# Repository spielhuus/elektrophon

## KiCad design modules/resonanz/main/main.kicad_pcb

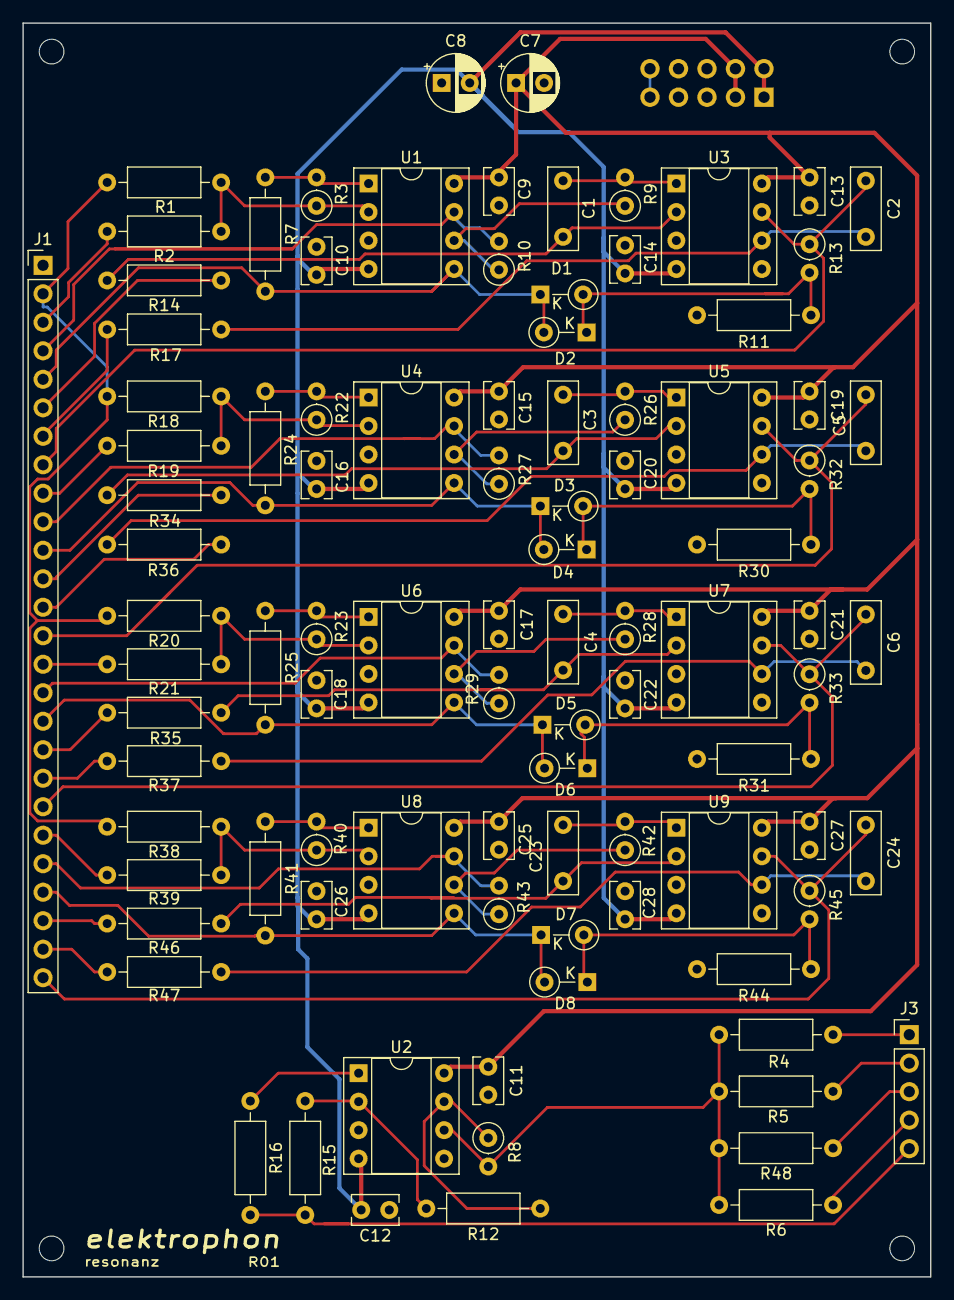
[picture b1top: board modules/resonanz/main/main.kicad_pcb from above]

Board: 2 copper layers, 80.9 x 111.8 mm, 101 parts (1 on the bottom side), 66 nets.

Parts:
C1, C2, C3, C4, C5, C6, C23, C24: 22n polyester; C_Rect_L7.2mm_W2.5mm_P5.00mm_FKS2_FKP2_MKS2_MKP2
C7, C8: 10u; CP_Radial_D5.0mm_P2.50mm
C9, C10, C11, C12, C13, C14, C15, C16, C17, C18, C19, C20, C21, C22, C25, C26, C27, C28: 0.1u; C_Rect_L4.0mm_W2.5mm_P2.50mm
D1, D2, D3, D4, D5, D6, D7, D8: 1N4148; D_DO-35_SOD27_P3.81mm_Vertical_KathodeUp
H1, H2, H3, H4: MountingHole; MountingHole_2.2mm_M2
J1: Conn_01x26_Female; PinHeader_1x26_P2.54mm_Vertical
J2: IDC Header; IDC-Header_2x05_P2.54mm_Vertical
J3: Conn_01x05_Female; PinHeader_1x05_P2.54mm_Vertical
R1, R2, R18, R19, R20, R21, R38, R39: 47k; R_Axial_DIN0207_L6.3mm_D2.5mm_P10.16mm_Horizontal
R3, R22, R23, R40: 47k; R_Axial_DIN0207_L6.3mm_D2.5mm_P2.54mm_Vertical
R4, R5, R6, R12, R15, R48: 100k; R_Axial_DIN0207_L6.3mm_D2.5mm_P10.16mm_Horizontal
R7, R24, R25, R41: 10k; R_Axial_DIN0207_L6.3mm_D2.5mm_P10.16mm_Horizontal
R8: 100k; R_Axial_DIN0207_L6.3mm_D2.5mm_P2.54mm_Vertical
R9, R10, R26, R27, R28, R29, R42, R43: 10k; R_Axial_DIN0207_L6.3mm_D2.5mm_P2.54mm_Vertical
R11, R30, R31, R44: 15k; R_Axial_DIN0207_L6.3mm_D2.5mm_P10.16mm_Horizontal
R13, R32, R33, R45: 6k8; R_Axial_DIN0207_L6.3mm_D2.5mm_P2.54mm_Vertical
R14, R17, R34, R35, R36, R37, R46, R47: 680; R_Axial_DIN0207_L6.3mm_D2.5mm_P10.16mm_Horizontal
R16: 1k; R_Axial_DIN0207_L6.3mm_D2.5mm_P10.16mm_Horizontal
REF1: elektrophon logo
U1, U3, U4, U5, U6, U7, U8, U9: LM1458; DIP-8_W7.62mm_Socket
U2: TL072; DIP-8_W7.62mm_Socket

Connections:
+5V: J2.9, J2.10
+15V: C7.1, C9.1, C11.1, C13.1, C15.1, C17.1, C19.1, C21.1, C25.1, C27.1, J2.3, J2.4, U1.8, U2.8, U3.8, U4.8, U5.8, U6.8, U7.8, U8.8, U9.8
-15V: C8.2, C10.2, C12.2, C14.2, C16.2, C18.2, C20.2, C22.2, C26.2, C28.2, J2.1, J2.2, U1.4, U2.4, U3.4, U4.4, U5.4, U6.4, U7.4, U8.4, U9.4
FREQ_1_a: J1.4, R10.2, U1.7
FREQ_1_b: J1.7, R17.2
FREQ_1_c: J1.6, R14.2
FREQ_2_a: J1.10, R27.2, U4.7
FREQ_2_b: J1.13, R36.2
FREQ_2_c: J1.12, R34.2
FREQ_3_a: J1.16, R29.2, U6.7
FREQ_3_b: J1.19, R37.2
FREQ_3_c: J1.18, R35.2
FREQ_4_a: J1.22, R43.2, U8.7
FREQ_4_b: J1.25, R47.2
FREQ_4_c: J1.24, R46.2
GND: C7.2, C8.1, C9.2, C10.1, C11.2, C12.1, C13.2, C14.1, C15.2, C16.1, C17.2, C18.1, C19.2, C20.1, C21.2, C22.1, C25.2, C26.1, C27.2, C28.1, J1.1, J2.5, J2.6, J2.7, J2.8, R11.2, R30.2, R31.2, R44.2, U1.3, U2.3, U2.5, U3.3, U3.5, U4.3, U5.3, U5.5, U6.3, U7.3, U7.5, U8.3, U9.3, U9.5
IN: J1.2, R1.1, R18.1, R20.1, R38.1
IN_1: J1.3, R2.1
IN_2: J1.9, R19.1
IN_3: J1.15, R21.1
IN_4: J1.21, R39.1
MIX_1: J3.1, R4.2
MIX_2: J3.2, R5.2
MIX_3: J3.3, R48.2
MIX_4: J3.4, R6.2
unnamed: C1.1, R9.2, U3.1
unnamed: C1.2, R14.1, U3.2
unnamed: C2.2, R17.1, U3.6
unnamed: C3.1, R26.2, U5.1
unnamed: C3.2, R34.1, U5.2
unnamed: C4.1, R28.2, U7.1
unnamed: C4.2, R35.1, U7.2
unnamed: C5.2, R36.1, U5.6
unnamed: C6.2, R37.1, U7.6
unnamed: C23.1, R42.2, U9.1
unnamed: C23.2, R46.1, U9.2
unnamed: C24.2, R47.1, U9.6
unnamed: D1.2, D2.1, R11.1, R13.2
unnamed: D3.2, D4.1, R30.1, R32.2
unnamed: D5.2, D6.1, R31.1, R33.2
unnamed: D7.2, D8.1, R44.1, R45.2
unnamed: R1.2, R2.2, R3.1, U1.2
unnamed: R3.2, R7.1, U1.1
unnamed: R4.1, R5.1, R6.1, R8.2, R48.1, U2.6
unnamed: R9.1, R10.1, U1.6
unnamed: R12.1, R15.2, U2.2
unnamed: R8.1, R12.2, U2.7
unnamed: R16.2, U2.1
unnamed: R18.2, R19.2, R22.1, U4.2
unnamed: R20.2, R21.2, R23.1, U6.2
unnamed: R22.2, R24.1, U4.1
unnamed: R23.2, R25.1, U6.1
unnamed: R26.1, R27.1, U4.6
unnamed: R28.1, R29.1, U6.6
unnamed: R38.2, R39.2, R40.1, U8.2
unnamed: R40.2, R41.1, U8.1
unnamed: R42.1, R43.1, U8.6
OUT: J3.5, R15.1, R16.1
OUT_1: C2.1, J1.8, R13.1, U3.7
OUT_2: C5.1, J1.14, R32.1, U5.7
OUT_3: C6.1, J1.20, R33.1, U7.7
OUT_4: C24.1, J1.26, R45.1, U9.7
RES_1: D1.1, D2.2, J1.5, R7.2, U1.5
RES_2: D3.1, D4.2, J1.11, R24.2, U4.5
RES_3: D5.1, D6.2, J1.17, R25.2, U6.5
RES_4: D7.1, D8.2, J1.23, R41.2, U8.5

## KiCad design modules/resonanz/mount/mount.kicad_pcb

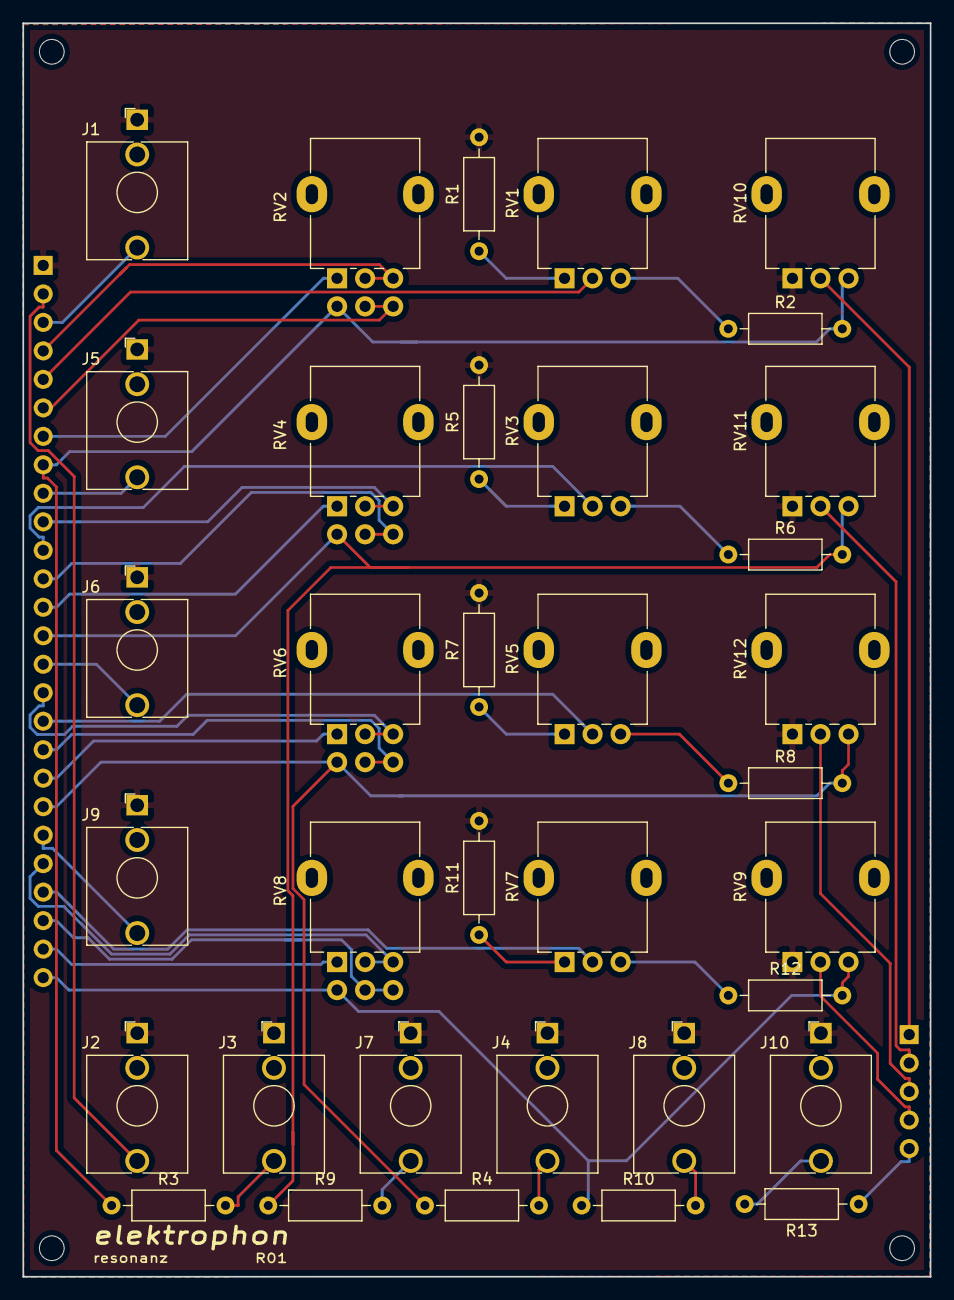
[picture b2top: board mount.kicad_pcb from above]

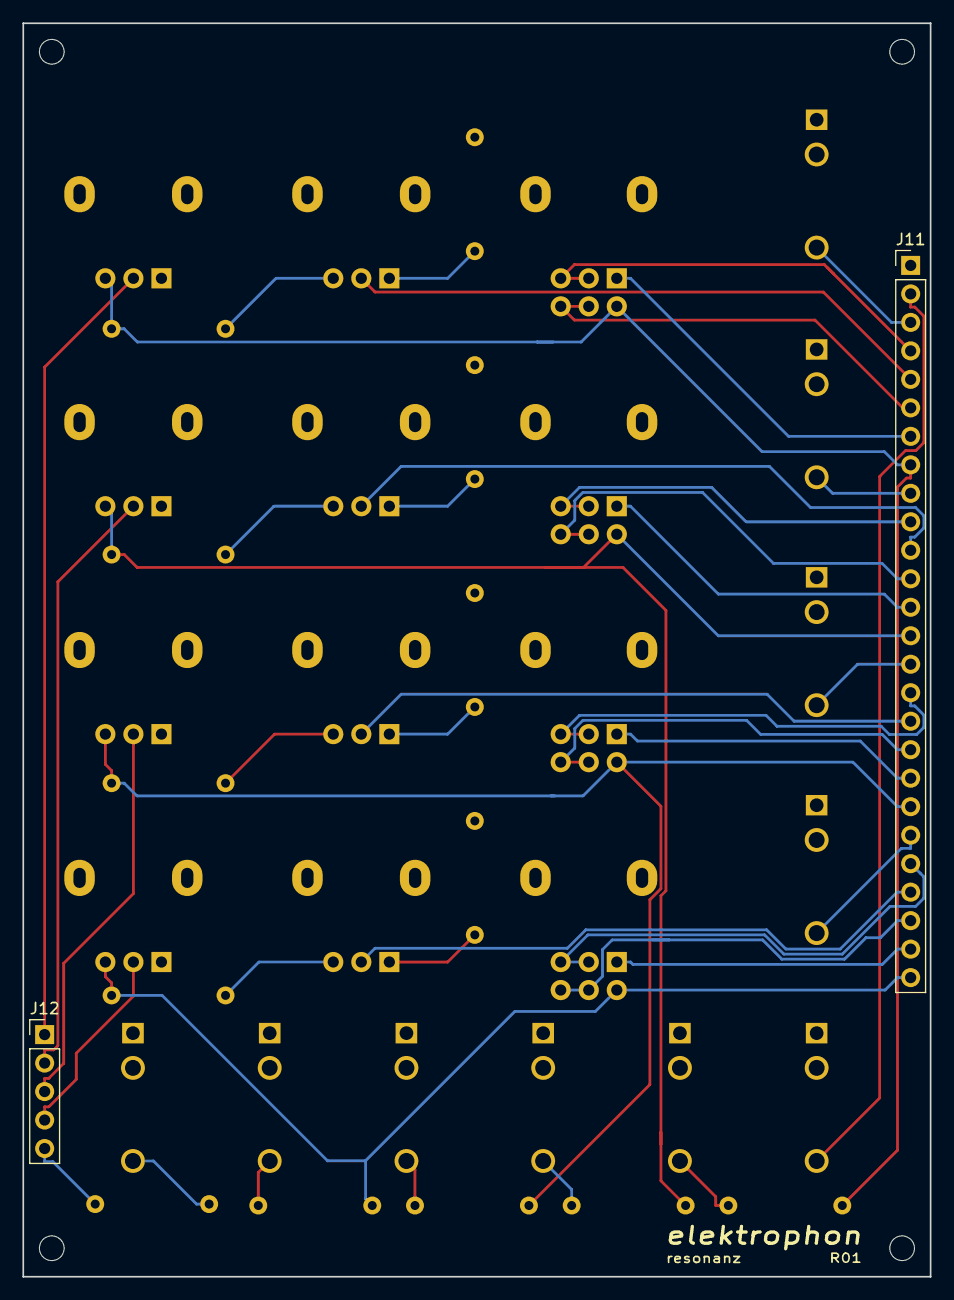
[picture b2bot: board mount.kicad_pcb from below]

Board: 2 copper layers, 80.9 x 111.8 mm, 41 parts (2 on the bottom side), 44 nets.

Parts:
H1, H2, H3, H4: MountingHole; MountingHole_2.2mm_M2
J1, J2, J3, J4, J5, J6, J7, J8, J9, J10: AudioJack2_SwitchT; Jack_3.5mm_WQP-PJ398SM_Vertical
J11: Conn_01x26_Male; PinHeader_1x26_P2.54mm_Vertical
J12: Conn_01x05_Male; PinHeader_1x05_P2.54mm_Vertical
R1, R5, R7, R11: 470; R_Axial_DIN0207_L6.3mm_D2.5mm_P10.16mm_Horizontal
R2, R6, R8, R12: 22k; R_Axial_DIN0207_L6.3mm_D2.5mm_P10.16mm_Horizontal
R3, R4, R9, R10, R13: 1k; R_Axial_DIN0207_L6.3mm_D2.5mm_P10.16mm_Horizontal
RV1, RV3, RV5, RV7: 50k; Potentiometer_Alpha_RD901F-40-00D_Single_Vertical
RV2, RV4, RV6, RV8: 100k; Potentiometer_Alpha_RD902F-40-00D_Dual_Vertical
RV9, RV10, RV11, RV12: 100k; Potentiometer_Alpha_RD901F-40-00D_Single_Vertical

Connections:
FREQ_1_a: J11.4, RV2.2, RV2.3
FREQ_1_b: J11.7, RV2.1
FREQ_1_c: J11.6, RV2.5, RV2.6
FREQ_2_a: J11.10, RV4.2, RV4.3
FREQ_2_b: J11.13, RV4.1
FREQ_2_c: J11.12, RV4.5, RV4.6
FREQ_3_a: J11.16, RV6.2, RV6.3
FREQ_3_b: J11.19, RV6.1
FREQ_3_c: J11.18, RV6.5, RV6.6
FREQ_4_a: J11.22, RV8.2, RV8.3
FREQ_4_b: J11.25, RV8.1
FREQ_4_c: J11.24, RV8.5, RV8.6
GND: J1.S, J2.S, J3.S, J4.S, J5.S, J6.S, J7.S, J8.S, J9.S, J10.S, J11.1, R1.2, R5.2, R7.2, R11.2, RV9.1, RV10.1, RV11.1, RV12.1
IN: J2.T, J11.2
IN_1: J1.T, J11.3
IN_2: J5.T, J11.9
IN_3: J6.T, J11.15
IN_4: J9.T, J11.21
MIX_1: J12.1, RV10.2
MIX_2: J12.2, RV11.2
MIX_3: J12.3, RV12.2
MIX_4: J12.4, RV9.2
unnamed: J3.T, R3.2
unnamed: J4.T, R4.2
unnamed: J7.T, R9.2
unnamed: J8.T, R10.2
unnamed: J10.T, R13.2
unnamed: R1.1, RV1.1
unnamed: R2.1, RV1.3
unnamed: R5.1, RV3.1
unnamed: R6.1, RV3.3
unnamed: R7.1, RV5.1
unnamed: R8.1, RV5.3
unnamed: R11.1, RV7.1
unnamed: R12.1, RV7.3
OUT: J12.5, R13.1
OUT_1: J11.8, R2.2, R3.1, RV2.4, RV10.3
OUT_2: J11.14, R6.2, R9.1, RV4.4, RV11.3
OUT_3: J11.20, R4.1, R8.2, RV6.4, RV12.3
OUT_4: J11.26, R10.1, R12.2, RV8.4, RV9.3
RES_1: J11.5, RV1.2
RES_2: J11.11, RV3.2
RES_3: J11.17, RV5.2
RES_4: J11.23, RV7.2

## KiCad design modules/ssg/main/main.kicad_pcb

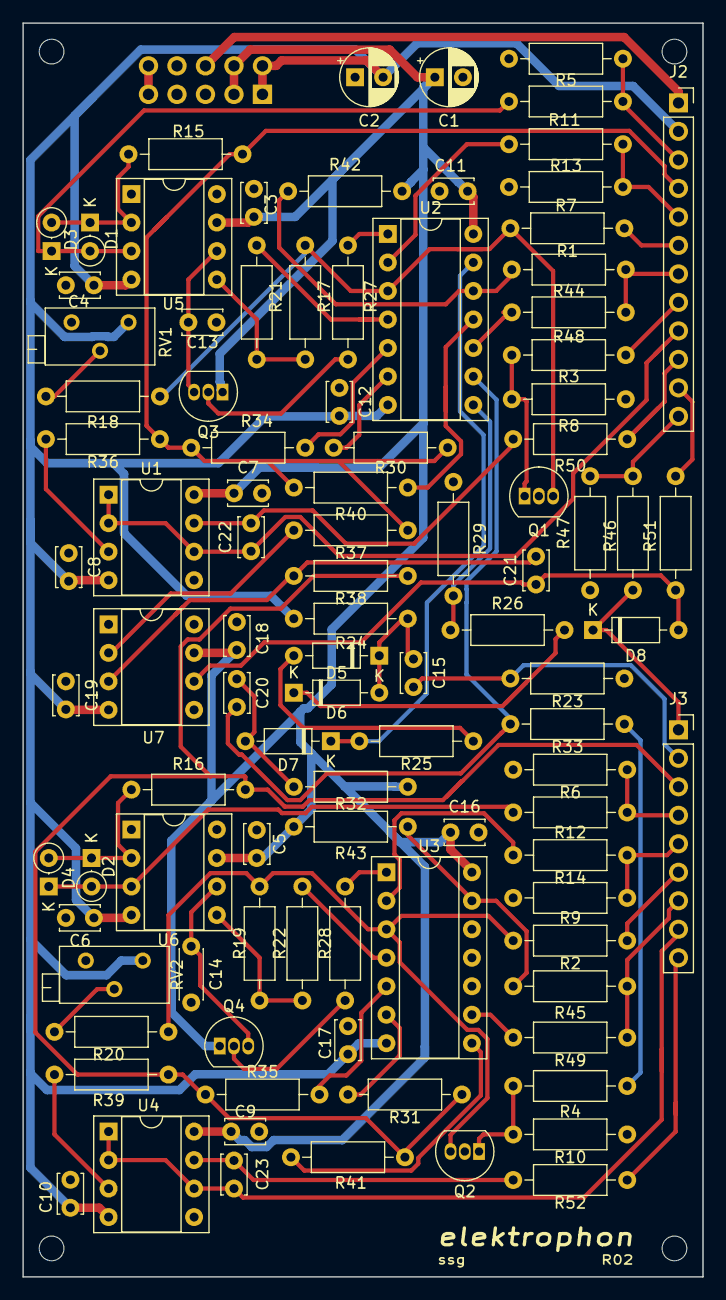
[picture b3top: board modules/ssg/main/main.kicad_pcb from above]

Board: 2 copper layers, 60.6 x 111.8 mm, 99 parts (1 on the bottom side), 70 nets.

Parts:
C1, C2: 10u; CP_Radial_D5.0mm_P2.50mm
C3, C4, C5, C6, C7, C8, C9, C10, C11, C12, C16, C17, C18, C19: 0.1u; C_Disc_D3.4mm_W2.1mm_P2.50mm
C13: 100n; C_Disc_D3.4mm_W2.1mm_P2.50mm
C14: 220n; C_Disc_D4.3mm_W1.9mm_P5.00mm
C15, C20: 1n; C_Disc_D3.4mm_W2.1mm_P2.50mm
C21: 100p; C_Disc_D3.4mm_W2.1mm_P2.50mm
C22, C23: 47p; C_Disc_D3.4mm_W2.1mm_P2.50mm
D1, D2, D3, D4: 1N4148; D_DO-35_SOD27_P2.54mm_Vertical_KathodeUp
D5, D6, D7, D8: 1N4148; D_DO-35_SOD27_P7.62mm_Horizontal
J1: IDC Header; IDC-Header_2x05_P2.54mm_Vertical
J2: Conn_01x12_Female; PinSocket_1x12_P2.54mm_Vertical
J3: Conn_01x09_Female; PinSocket_1x09_P2.54mm_Vertical
Q1, Q2: PN4250; TO-92_Inline
Q3, Q4: J201; TO-92_Inline
R1, R2, R13, R14: 2M7; R_Axial_DIN0207_L6.3mm_D2.5mm_P10.16mm_Horizontal
R3, R4, R5, R6, R11, R12, R15, R16, R24: 33k; R_Axial_DIN0207_L6.3mm_D2.5mm_P10.16mm_Horizontal
R7, R9, R23, R26: 100k; R_Axial_DIN0207_L6.3mm_D2.5mm_P10.16mm_Horizontal
R8, R10, R21, R22: 15k; R_Axial_DIN0207_L6.3mm_D2.5mm_P10.16mm_Horizontal
R17, R19: 82k; R_Axial_DIN0207_L6.3mm_D2.5mm_P10.16mm_Horizontal
R18, R20, R32: 1M5; R_Axial_DIN0207_L6.3mm_D2.5mm_P10.16mm_Horizontal
R25: 680k; R_Axial_DIN0207_L6.3mm_D2.5mm_P10.16mm_Horizontal
R27, R31: 820k; R_Axial_DIN0207_L6.3mm_D2.5mm_P10.16mm_Horizontal
R28, R30, R42, R43: 1M; R_Axial_DIN0207_L6.3mm_D2.5mm_P10.16mm_Horizontal
R29: 4M7; R_Axial_DIN0207_L6.3mm_D2.5mm_P10.16mm_Horizontal
R33, R34, R35: 330; R_Axial_DIN0207_L6.3mm_D2.5mm_P10.16mm_Horizontal
R36, R37, R38, R39: 10k; R_Axial_DIN0207_L6.3mm_D2.5mm_P10.16mm_Horizontal
R40, R41: 470k; R_Axial_DIN0207_L6.3mm_D2.5mm_P10.16mm_Horizontal
R44, R45: 2M2; R_Axial_DIN0207_L6.3mm_D2.5mm_P10.16mm_Horizontal
R46, R47, R48, R49, R51: 3k3; R_Axial_DIN0207_L6.3mm_D2.5mm_P10.16mm_Horizontal
R50, R52: 100; R_Axial_DIN0207_L6.3mm_D2.5mm_P10.16mm_Horizontal
RV1, RV2: 25k; Potentiometer_Bourns_3296Z_Horizontal
U1, U4: TL072; DIP-8_W7.62mm_Socket
U2, U3: LM3900; DIP-14_W7.62mm_Socket
U5, U6: CA3080; DIP-8_W7.62mm_Socket
U7: LM741; DIP-8_W7.62mm_Socket

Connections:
+5V: J1.9, J1.10
+15V: C1.1, C3.1, C5.1, C7.1, C9.1, C11.1, C16.1, C18.1, J1.3, J1.4, Q3.1, Q4.1, R32.2, R42.2, R43.2, U1.8, U2.14, U3.14, U4.8, U5.7, U6.7, U7.7
-15V: C2.2, C4.2, C6.2, C8.2, C10.2, C12.2, C17.2, C19.2, J1.1, J1.2, J2.2, R24.1, RV1.1, RV2.1, U1.4, U2.7, U3.7, U4.4, U5.4, U6.4, U7.4
/HOLD: R4.2, R33.1
COUPLER_5V: J2.12, R46.1, R47.2
COUPLER_HOT: J2.11, R51.1
CYCLE_1: J2.7, R44.1, R48.1
CYCLE_2: J3.7, R45.1, R49.1
GND: C1.2, C2.1, C3.2, C4.1, C5.2, C6.1, C7.2, C8.1, C9.2, C10.1, C11.2, C12.1, C13.2, C14.2, C16.2, C17.1, C18.2, C19.1, J1.5, J1.6, J1.7, J1.8, J2.1, Q1.2, Q2.2, R5.1, R6.1, R7.1, R8.1, R9.1, R10.1, R23.1, R29.1, R47.1, RV1.3, RV2.3, U1.5, U4.5
HOLD_1: J2.8, R3.2
IN_1: J2.3, R5.2, R11.2
IN_2: J3.4, R6.2, R12.2
LED: D8.1, J3.1, R46.2
LED_1_a: C22.1, J2.9, U1.1, U1.2, U1.6
LED_1_b: J2.10, R50.1
LED_2_a: C23.1, J3.8, U4.1, U4.2, U4.6
LED_2_b: J3.9, R52.1
unnamed: C13.1, Q3.3, U5.6
unnamed: C14.1, Q4.3, U6.6
unnamed: C15.2, D5.1, D6.2, R24.2
unnamed: C20.1, R33.2, U2.9
unnamed: C20.2, D7.2, R32.1
unnamed: C21.1, D8.2, R51.2, U7.6
unnamed: C21.2, R38.1, U7.3
unnamed: C22.2, R50.2, U1.7
unnamed: C23.2, R52.2, U4.7
unnamed: D1.1, D3.2, R15.2, U5.2
unnamed: D1.2, D3.1, R11.1, U5.3
unnamed: D2.1, D4.2, R16.2, U6.2
unnamed: D2.2, D4.1, R12.1, U6.3
unnamed: D5.2, R25.2
unnamed: D6.1, R26.2
unnamed: D7.1, R25.1, U2.13
unnamed: Q1.1, R3.1, R8.2
unnamed: Q1.3, R1.1, R17.2, R18.2, U2.3
unnamed: Q2.1, R4.1, R10.2
unnamed: Q2.3, R2.1, R19.2, R20.2, U3.3
unnamed: Q3.2, R27.2
unnamed: Q4.2, R28.2
unnamed: R13.1, U2.2
unnamed: R14.1, U3.2
unnamed: R17.1, R21.1, U5.5
unnamed: R18.1, RV1.2
unnamed: R19.1, R22.1, U6.5
unnamed: R20.1, RV2.2
unnamed: R21.2, U2.4
unnamed: R22.2, U3.4
unnamed: R26.1, R29.2, U2.8
unnamed: R27.1, U2.1
unnamed: R28.1, U3.1
unnamed: R30.1, U2.6
unnamed: R31.1, U3.6
unnamed: R34.2, U2.5
unnamed: R35.2, U3.5
unnamed: R36.1, U1.3
unnamed: R37.1, U7.2
unnamed: R39.1, U4.3
unnamed: R40.1, U2.11
unnamed: R41.1, U3.8
unnamed: R42.1, R44.2, U2.12
unnamed: R43.1, R45.2, U3.13
unnamed: R48.2, U2.10
unnamed: R49.2, U3.9
OUT_1: J2.4, R15.1, R30.2, R34.1, R36.2, R37.2, R40.2
OUT_2: J3.3, R16.1, R31.2, R35.1, R38.2, R39.2, R41.2
RATE_1: J2.6, R1.2
RATE_2: J3.6, R2.2
SAMPLE_2: C15.1, J3.2, R23.2
VC_1: J2.5, R7.2, R13.2
VC_2: J3.5, R9.2, R14.2

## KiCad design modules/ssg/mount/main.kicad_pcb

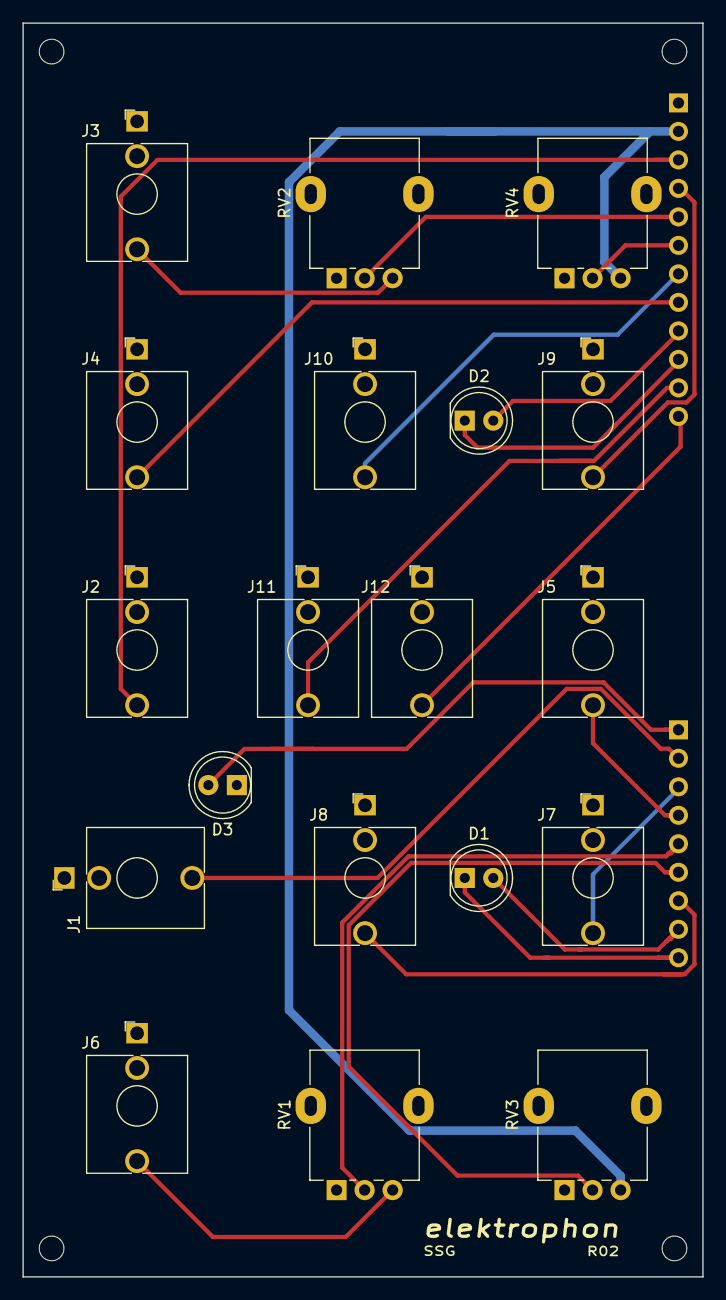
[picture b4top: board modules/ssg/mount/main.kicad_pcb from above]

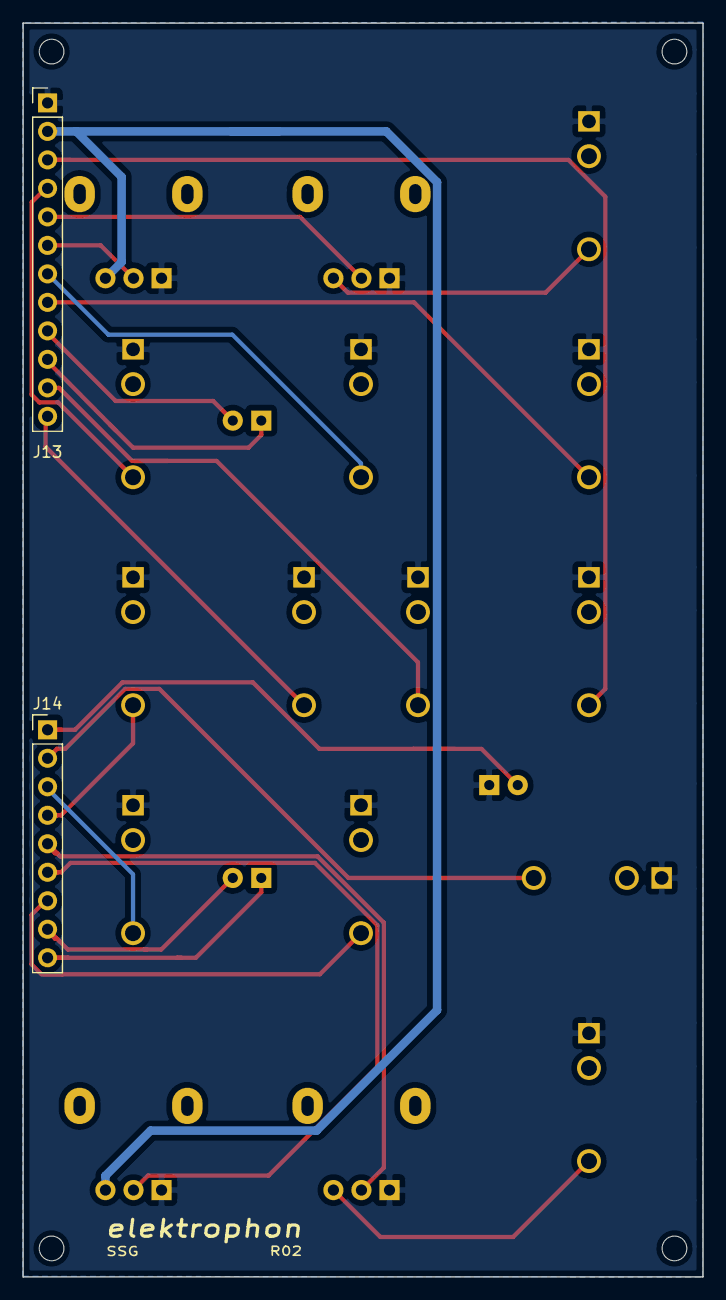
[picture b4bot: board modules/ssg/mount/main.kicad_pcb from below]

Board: 2 copper layers, 60.6 x 111.8 mm, 21 parts (2 on the bottom side), 23 nets.

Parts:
D1, D2: LED_Dual_2pin; LED_D5.0mm
D3: LED; LED_D5.0mm
J1: SAMPLE; Jack_3.5mm_WQP-PJ398SM_Vertical
J2, J5: IN; Jack_3.5mm_WQP-PJ398SM_Vertical
J3, J6: VC; Jack_3.5mm_WQP-PJ398SM_Vertical
J4: HOLD; Jack_3.5mm_WQP-PJ398SM_Vertical
J7, J9: OUT; Jack_3.5mm_WQP-PJ398SM_Vertical
J8, J10: CYCLE; Jack_3.5mm_WQP-PJ398SM_Vertical
J11: HOT; Jack_3.5mm_WQP-PJ398SM_Vertical
J12: 5V; Jack_3.5mm_WQP-PJ398SM_Vertical
J13: Conn_01x12_Male; PinHeader_1x12_P2.54mm_Vertical
J14: Conn_01x09_Male; PinHeader_1x09_P2.54mm_Vertical
RV1, RV2, RV3, RV4: 50k; Potentiometer_Alpha_RD901F-40-00D_Single_Vertical

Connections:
-15V: J13.2, RV3.3, RV4.3
COUPLER_5V: J12.T, J13.12
COUPLER_HOT: J11.T, J13.11
CYCLE_1: J10.T, J13.7
CYCLE_2: J8.T, J14.7
GND: D3.1, J1.S, J2.S, J3.S, J4.S, J5.S, J6.S, J7.S, J8.S, J9.S, J10.S, J11.S, J12.S, J13.1, RV1.1, RV2.1, RV3.1, RV4.1
HOLD_1: J4.T, J13.8
IN_1: J2.T, J13.3
IN_2: J5.T, J14.4
LED: D3.2, J14.1
LED_1_a: D2.2, J13.9
LED_1_b: D2.1, J13.10
LED_2_a: D1.2, J14.8
LED_2_b: D1.1, J14.9
unnamed: J3.T, RV2.3
unnamed: J6.T, RV1.3
OUT_1: J9.T, J13.4
OUT_2: J7.T, J14.3
RATE_1: J13.6, RV4.2
RATE_2: J14.6, RV3.2
SAMPLE_2: J1.T, J14.2
VC_1: J13.5, RV2.2
VC_2: J14.5, RV1.2

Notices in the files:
modules/resonanz/main/main.kicad_pcb:
License CC BY 4.0 - Attribution 4.0 International
